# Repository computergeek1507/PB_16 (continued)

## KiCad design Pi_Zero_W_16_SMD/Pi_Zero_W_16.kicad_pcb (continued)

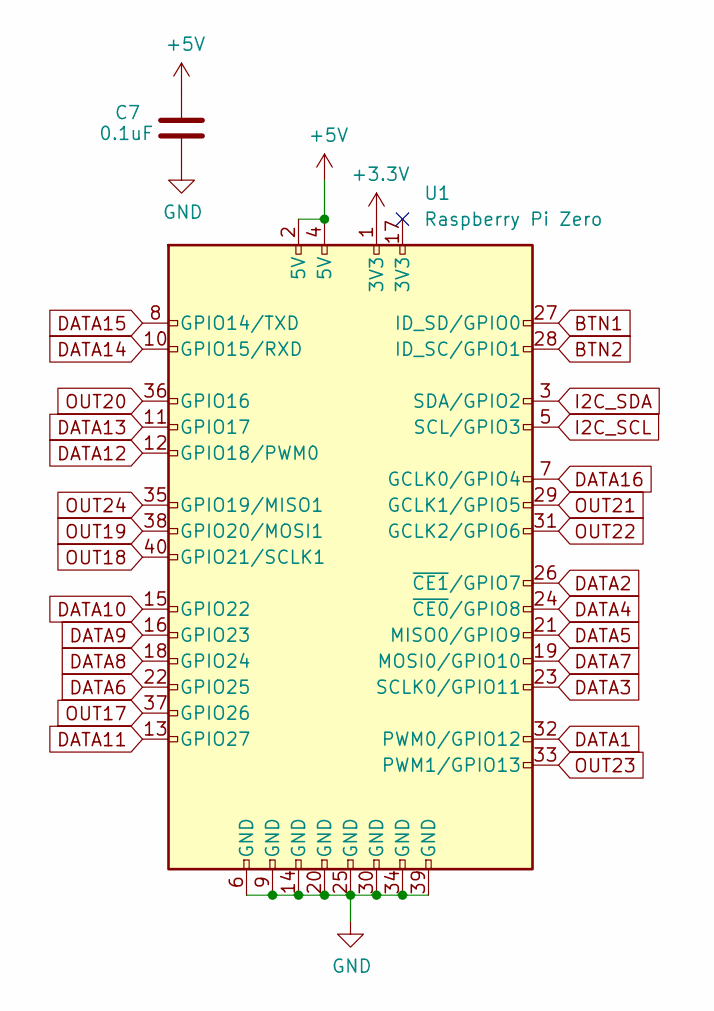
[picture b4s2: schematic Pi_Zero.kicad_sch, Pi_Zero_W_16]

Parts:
C7: 0.1uF; C_0603_1608Metric_Pad1.08x0.95mm_HandSolder
U1: Raspberry Pi Zero; Raspberry_Pi_Zero_Socketed_THT_FaceDown_MountingHoles

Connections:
+3V3: U1.1 (3V3); also elsewhere on the board
+5V: C7.1, U1.2 (5V), U1.4 (5V); also elsewhere on the board
BTN1: U1.27 (ID_SD/GPIO0); also elsewhere on the board
BTN2: U1.28 (ID_SC/GPIO1); also elsewhere on the board
DATA1: U1.32 (PWM0/GPIO12); also elsewhere on the board
DATA2: U1.26 (~CE1/GPIO7); also elsewhere on the board
DATA3: U1.23 (SCLK0/GPIO11); also elsewhere on the board
DATA4: U1.24 (~CE0/GPIO8); also elsewhere on the board
DATA5: U1.21 (MISO0/GPIO9); also elsewhere on the board
DATA6: U1.22 (GPIO25); also elsewhere on the board
DATA7: U1.19 (MOSI0/GPIO10); also elsewhere on the board
DATA8: U1.18 (GPIO24); also elsewhere on the board
DATA9: U1.16 (GPIO23); also elsewhere on the board
DATA10: U1.15 (GPIO22); also elsewhere on the board
DATA11: U1.13 (GPIO27); also elsewhere on the board
DATA12: U1.12 (GPIO18/PWM0); also elsewhere on the board
DATA13: U1.11 (GPIO17); also elsewhere on the board
DATA14: U1.10 (GPIO15/RXD); also elsewhere on the board
DATA15: U1.8 (GPIO14/TXD); also elsewhere on the board
DATA16: U1.7 (GCLK0/GPIO4); also elsewhere on the board
GND: C7.2, U1.6 (GND), U1.9 (GND), U1.14 (GND), U1.20 (GND), U1.25 (GND), U1.30 (GND), U1.34 (GND), U1.39 (GND); also elsewhere on the board
I2C_SCL: U1.5 (SCL/GPIO3); also elsewhere on the board
I2C_SDA: U1.3 (SDA/GPIO2); also elsewhere on the board
OUT17: U1.37 (GPIO26); also elsewhere on the board
OUT18: U1.40 (GPIO21/SCLK1); also elsewhere on the board
OUT19: U1.38 (GPIO20/MOSI1); also elsewhere on the board
OUT20: U1.36 (GPIO16); also elsewhere on the board
OUT21: U1.29 (GCLK1/GPIO5); also elsewhere on the board
OUT22: U1.31 (GCLK2/GPIO6); also elsewhere on the board
OUT23: U1.33 (PWM1/GPIO13); also elsewhere on the board
OUT24: U1.35 (GPIO19/MISO1); also elsewhere on the board

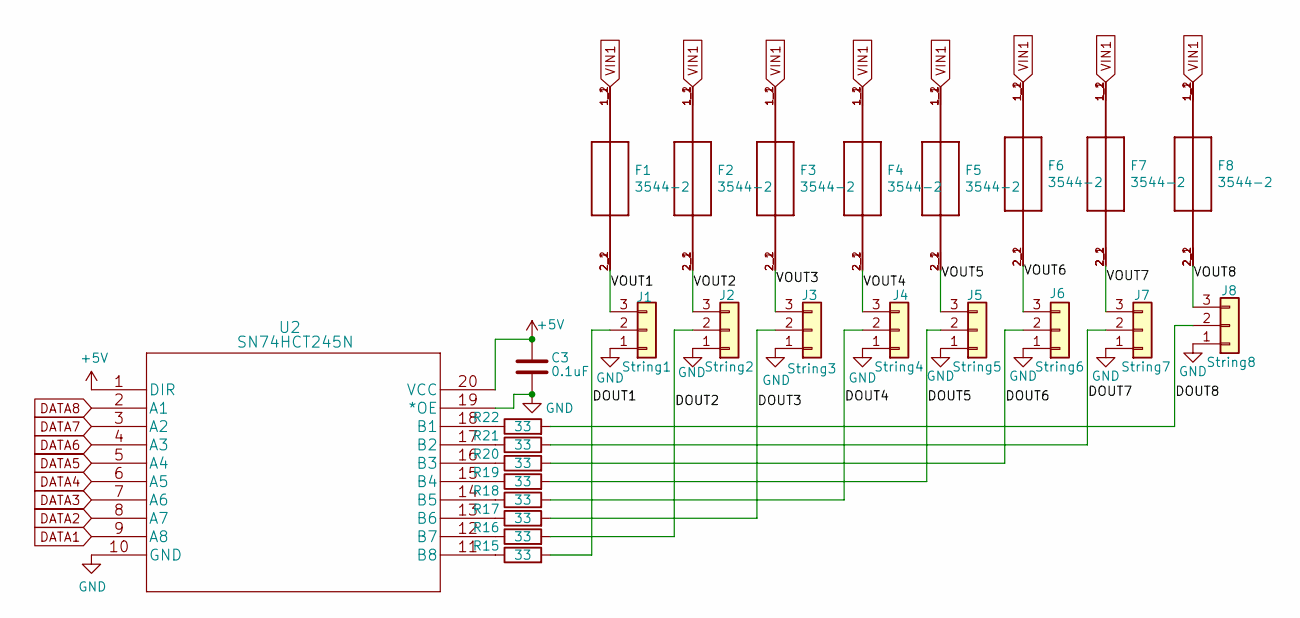
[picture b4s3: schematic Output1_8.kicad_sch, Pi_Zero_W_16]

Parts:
C3: 0.1uF; C_0603_1608Metric_Pad1.08x0.95mm_HandSolder; MPN CL10B104KB8NNWC; Digi-Key_PN 1276-1935-2-ND
F1, F2, F3, F4, F5, F6, F7, F8: 3544-2; FUSE_3544-2; MPN 3544-2; Digi-Key_PN 36-3544-2-ND
J1: String1; PhoenixContact_MCV_3.81mm_3.5mm_1x03_Vertical; MPN 1843619/OSTTJ0311530; Digi-Key_PN 277-5737-ND/ED10555-ND
J2: String2; PhoenixContact_MCV_3.81mm_3.5mm_1x03_Vertical; MPN 1843619/OSTTJ0311530; Digi-Key_PN 277-5737-ND/ED10555-ND
J3: String3; PhoenixContact_MCV_3.81mm_3.5mm_1x03_Vertical; MPN 1843619/OSTTJ0311530; Digi-Key_PN 277-5737-ND/ED10555-ND
J4: String4; PhoenixContact_MCV_3.81mm_3.5mm_1x03_Vertical; MPN 1843619/OSTTJ0311530; Digi-Key_PN 277-5737-ND/ED10555-ND
J5: String5; PhoenixContact_MCV_3.81mm_3.5mm_1x03_Vertical; MPN 1843619/OSTTJ0311530; Digi-Key_PN 277-5737-ND/ED10555-ND
J6: String6; PhoenixContact_MCV_3.81mm_3.5mm_1x03_Vertical; MPN 1843619/OSTTJ0311530; Digi-Key_PN 277-5737-ND/ED10555-ND
J7: String7; PhoenixContact_MCV_3.81mm_3.5mm_1x03_Vertical; MPN 1843619/OSTTJ0311530; Digi-Key_PN 277-5737-ND/ED10555-ND
J8: String8; PhoenixContact_MCV_3.81mm_3.5mm_1x03_Vertical; MPN 1843619/OSTTJ0311530; Digi-Key_PN 277-5737-ND/ED10555-ND
R15, R16, R17, R18, R19, R20, R21, R22: 33; R_0603_1608Metric_Pad0.98x0.95mm_HandSolder; MPN RC0603FR-0733RL; LCSC C23140
U2: SN74HCT245N; SN74HCT245NSR; MPN SN74HCT245NSR; Digi-Key_PN 296-15849-1-ND

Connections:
+5V: C3.1, U2.1 (DIR), U2.20 (VCC); also elsewhere on the board
/Output 1-8/DOUT1: J1.2, R15.2
/Output 1-8/DOUT2: J2.2, R16.2
/Output 1-8/DOUT3: J3.2, R17.2
/Output 1-8/DOUT4: J4.2, R18.2
/Output 1-8/DOUT5: J5.2, R19.2
/Output 1-8/DOUT6: J6.2, R20.2
/Output 1-8/DOUT7: J7.2, R21.2
/Output 1-8/DOUT8: J8.2, R22.2
/Output 1-8/VOUT1: F1.2_1 (2), F1.2_2 (2), J1.3
/Output 1-8/VOUT2: F2.2_1 (2), F2.2_2 (2), J2.3
/Output 1-8/VOUT3: F3.2_1 (2), F3.2_2 (2), J3.3
/Output 1-8/VOUT4: F4.2_1 (2), F4.2_2 (2), J4.3
/Output 1-8/VOUT5: F5.2_1 (2), F5.2_2 (2), J5.3
/Output 1-8/VOUT6: F6.2_1 (2), F6.2_2 (2), J6.3
/Output 1-8/VOUT7: F7.2_1 (2), F7.2_2 (2), J7.3
/Output 1-8/VOUT8: F8.2_1 (2), F8.2_2 (2), J8.3
DATA1: U2.9 (A8); also elsewhere on the board
DATA2: U2.8 (A7); also elsewhere on the board
DATA3: U2.7 (A6); also elsewhere on the board
DATA4: U2.6 (A5); also elsewhere on the board
DATA5: U2.5 (A4); also elsewhere on the board
DATA6: U2.4 (A3); also elsewhere on the board
DATA7: U2.3 (A2); also elsewhere on the board
DATA8: U2.2 (A1); also elsewhere on the board
GND: C3.2, J1.1, J2.1, J3.1, J4.1, J5.1, J6.1, J7.1, J8.1, U2.10 (GND), U2.19 (*OE); also elsewhere on the board
unnamed: R15.1, U2.11 (B8)
unnamed: R16.1, U2.12 (B7)
unnamed: R17.1, U2.13 (B6)
unnamed: R18.1, U2.14 (B5)
unnamed: R19.1, U2.15 (B4)
unnamed: R20.1, U2.16 (B3)
unnamed: R21.1, U2.17 (B2)
unnamed: R22.1, U2.18 (B1)
VIN1: F1.1_1 (1), F1.1_2 (1), F2.1_1 (1), F2.1_2 (1), F3.1_1 (1), F3.1_2 (1), F4.1_1 (1), F4.1_2 (1), F5.1_1 (1), F5.1_2 (1), F6.1_1 (1), F6.1_2 (1), F7.1_1 (1), F7.1_2 (1), F8.1_1 (1), F8.1_2 (1); also elsewhere on the board

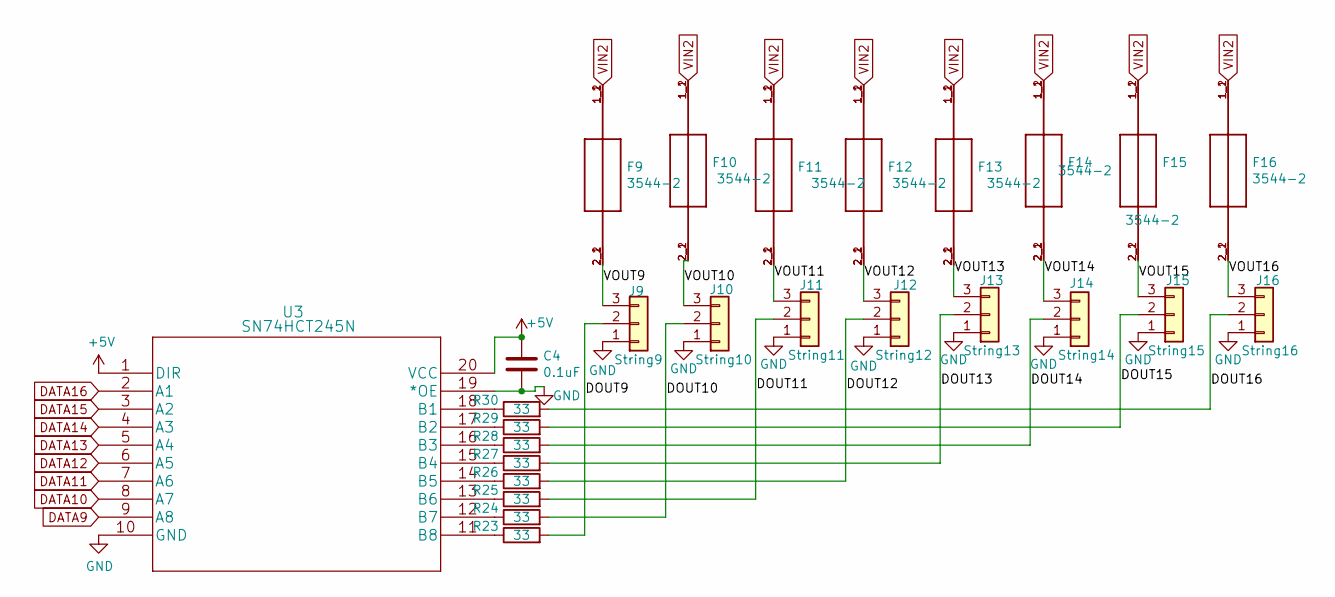
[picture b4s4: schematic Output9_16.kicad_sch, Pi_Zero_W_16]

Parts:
C4: 0.1uF; C_0603_1608Metric_Pad1.08x0.95mm_HandSolder; MPN CL10B104KB8NNWC; Digi-Key_PN 1276-1935-2-ND
F9, F10, F11, F12, F13, F14, F15, F16: 3544-2; FUSE_3544-2; MPN 3544-2; Digi-Key_PN 36-3544-2-ND
J9: String9; PhoenixContact_MCV_3.81mm_3.5mm_1x03_Vertical; MPN 1843619/OSTTJ0311530; Digi-Key_PN 277-5737-ND/ED10555-ND
J10: String10; PhoenixContact_MCV_3.81mm_3.5mm_1x03_Vertical; MPN 1843619/OSTTJ0311530; Digi-Key_PN 277-5737-ND/ED10555-ND
J11: String11; PhoenixContact_MCV_3.81mm_3.5mm_1x03_Vertical; MPN 1843619/OSTTJ0311530; Digi-Key_PN 277-5737-ND/ED10555-ND
J12: String12; PhoenixContact_MCV_3.81mm_3.5mm_1x03_Vertical; MPN 1843619/OSTTJ0311530; Digi-Key_PN 277-5737-ND/ED10555-ND
J13: String13; PhoenixContact_MCV_3.81mm_3.5mm_1x03_Vertical; MPN 1843619/OSTTJ0311530; Digi-Key_PN 277-5737-ND/ED10555-ND
J14: String14; PhoenixContact_MCV_3.81mm_3.5mm_1x03_Vertical; MPN 1843619/OSTTJ0311530; Digi-Key_PN 277-5737-ND/ED10555-ND
J15: String15; PhoenixContact_MCV_3.81mm_3.5mm_1x03_Vertical; MPN 1843619/OSTTJ0311530; Digi-Key_PN 277-5737-ND/ED10555-ND
J16: String16; PhoenixContact_MCV_3.81mm_3.5mm_1x03_Vertical; MPN 1843619/OSTTJ0311530; Digi-Key_PN 277-5737-ND/ED10555-ND
R23, R24, R25, R26, R27, R28, R29, R30: 33; R_0603_1608Metric_Pad0.98x0.95mm_HandSolder; MPN RC0603FR-0733RL; LCSC C23140
U3: SN74HCT245N; SN74HCT245NSR; MPN SN74HCT245NSR; Digi-Key_PN 296-15849-1-ND

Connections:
+5V: C4.1, U3.1 (DIR), U3.20 (VCC); also elsewhere on the board
/Output 9-16/DOUT9: J9.2, R23.2
/Output 9-16/DOUT10: J10.2, R24.2
/Output 9-16/DOUT11: J11.2, R25.2
/Output 9-16/DOUT12: J12.2, R26.2
/Output 9-16/DOUT13: J13.2, R27.2
/Output 9-16/DOUT14: J14.2, R28.2
/Output 9-16/DOUT15: J15.2, R29.2
/Output 9-16/DOUT16: J16.2, R30.2
/Output 9-16/VOUT9: F9.2_1 (2), F9.2_2 (2), J9.3
/Output 9-16/VOUT10: F10.2_1 (2), F10.2_2 (2), J10.3
/Output 9-16/VOUT11: F11.2_1 (2), F11.2_2 (2), J11.3
/Output 9-16/VOUT12: F12.2_1 (2), F12.2_2 (2), J12.3
/Output 9-16/VOUT13: F13.2_1 (2), F13.2_2 (2), J13.3
/Output 9-16/VOUT14: F14.2_1 (2), F14.2_2 (2), J14.3
/Output 9-16/VOUT15: F15.2_1 (2), F15.2_2 (2), J15.3
/Output 9-16/VOUT16: F16.2_1 (2), F16.2_2 (2), J16.3
DATA9: U3.9 (A8); also elsewhere on the board
DATA10: U3.8 (A7); also elsewhere on the board
DATA11: U3.7 (A6); also elsewhere on the board
DATA12: U3.6 (A5); also elsewhere on the board
DATA13: U3.5 (A4); also elsewhere on the board
DATA14: U3.4 (A3); also elsewhere on the board
DATA15: U3.3 (A2); also elsewhere on the board
DATA16: U3.2 (A1); also elsewhere on the board
GND: C4.2, J9.1, J10.1, J11.1, J12.1, J13.1, J14.1, J15.1, J16.1, U3.10 (GND), U3.19 (*OE); also elsewhere on the board
unnamed: R23.1, U3.11 (B8)
unnamed: R24.1, U3.12 (B7)
unnamed: R25.1, U3.13 (B6)
unnamed: R26.1, U3.14 (B5)
unnamed: R27.1, U3.15 (B4)
unnamed: R28.1, U3.16 (B3)
unnamed: R29.1, U3.17 (B2)
unnamed: R30.1, U3.18 (B1)
VIN2: F9.1_1 (1), F9.1_2 (1), F10.1_1 (1), F10.1_2 (1), F11.1_1 (1), F11.1_2 (1), F12.1_1 (1), F12.1_2 (1), F13.1_1 (1), F13.1_2 (1), F14.1_1 (1), F14.1_2 (1), F15.1_1 (1), F15.1_2 (1), F16.1_1 (1), F16.1_2 (1); also elsewhere on the board

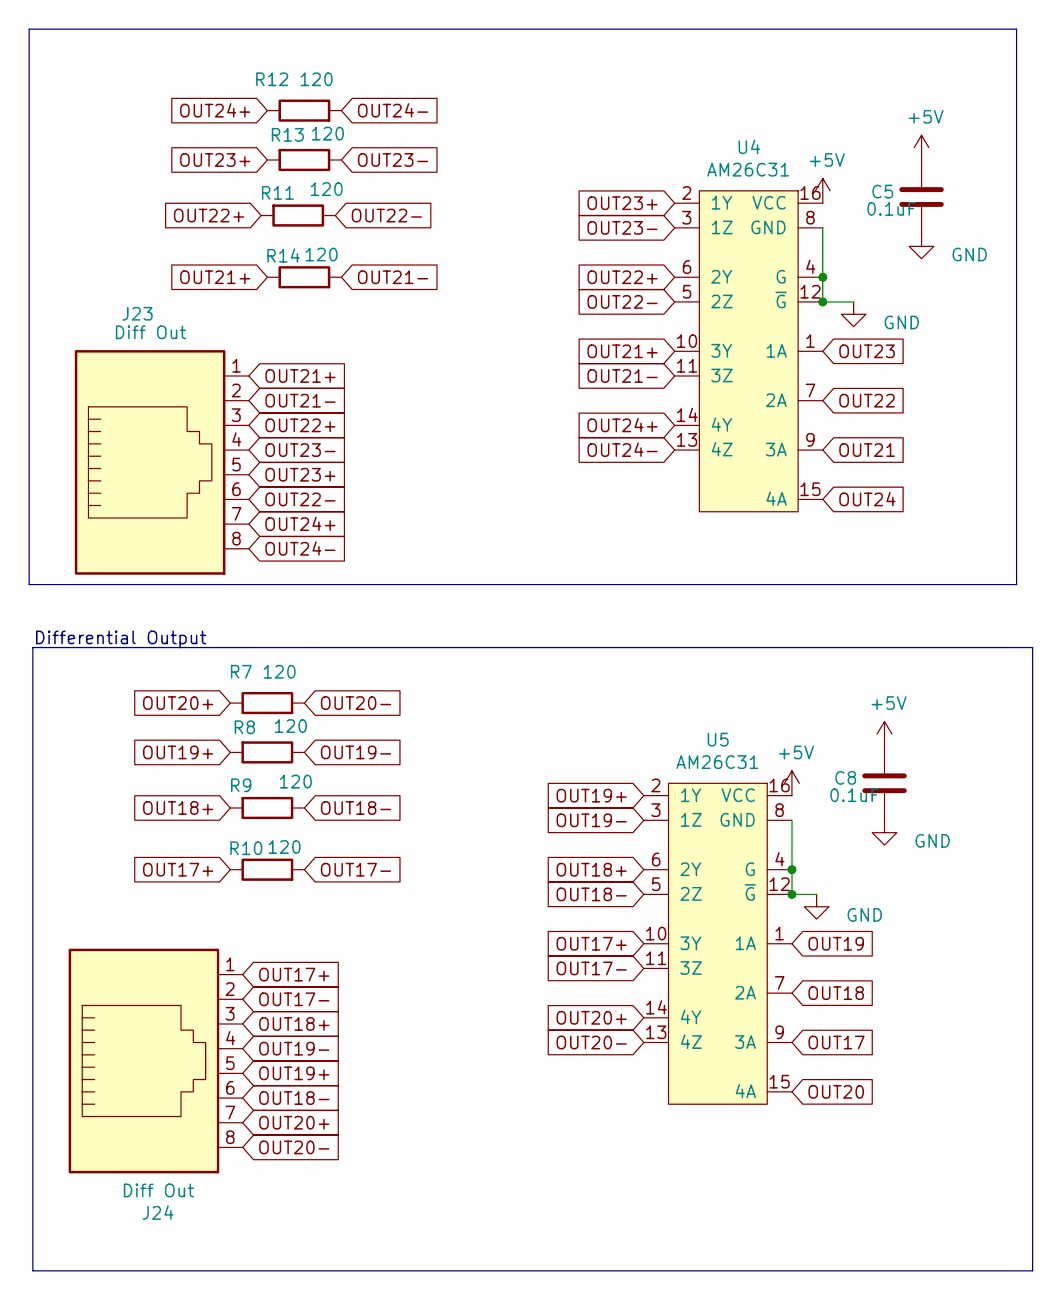
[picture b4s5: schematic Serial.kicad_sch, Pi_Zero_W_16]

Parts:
C5, C8: 0.1uF; C_0603_1608Metric_Pad1.08x0.95mm_HandSolder; MPN CL10B104KB8NNWC; Digi-Key_PN 1276-1935-2-ND
J23, J24: Diff Out; RJ45_Amphenol_54602-x08_Horizontal; MPN X05ADIWA1DY1022; Digi-Key_PN AE10392-ND
R7, R8, R9, R10, R11, R12, R13, R14: 120; R_0603_1608Metric_Pad0.98x0.95mm_HandSolder; MPN CRGCQ0603F120R; Digi-Key_PN A129677CT-ND
U4, U5: AM26C31; SOIC-16_3.9x9.9mm_P1.27mm; MPN AM26C31IDR; Farnell 4975637

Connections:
+5V: C5.1, C8.1, U4.16 (VCC), U5.16 (VCC); also elsewhere on the board
GND: C5.2, C8.2, U4.4 (G), U4.8 (GND), U4.12 (~G), U5.4 (G), U5.8 (GND), U5.12 (~G); also elsewhere on the board
OUT17: U5.9 (3A); also elsewhere on the board
OUT17+: J24.1, R10.1, U5.10 (3Y)
OUT17-: J24.2, R10.2, U5.11 (3Z)
OUT18: U5.7 (2A); also elsewhere on the board
OUT18+: J24.3, R9.2, U5.6 (2Y)
OUT18-: J24.6, R9.1, U5.5 (2Z)
OUT19: U5.1 (1A); also elsewhere on the board
OUT19+: J24.5, R8.2, U5.2 (1Y)
OUT19-: J24.4, R8.1, U5.3 (1Z)
OUT20: U5.15 (4A); also elsewhere on the board
OUT20+: J24.7, R7.1, U5.14 (4Y)
OUT20-: J24.8, R7.2, U5.13 (4Z)
OUT21: U4.9 (3A); also elsewhere on the board
OUT21+: J23.1, R14.1, U4.10 (3Y)
OUT21-: J23.2, R14.2, U4.11 (3Z)
OUT22: U4.7 (2A); also elsewhere on the board
OUT22+: J23.3, R11.2, U4.6 (2Y)
OUT22-: J23.6, R11.1, U4.5 (2Z)
OUT23: U4.1 (1A); also elsewhere on the board
OUT23+: J23.5, R13.2, U4.2 (1Y)
OUT23-: J23.4, R13.1, U4.3 (1Z)
OUT24: U4.15 (4A); also elsewhere on the board
OUT24+: J23.7, R12.1, U4.14 (4Y)
OUT24-: J23.8, R12.2, U4.13 (4Z)

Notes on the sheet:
Differential Output

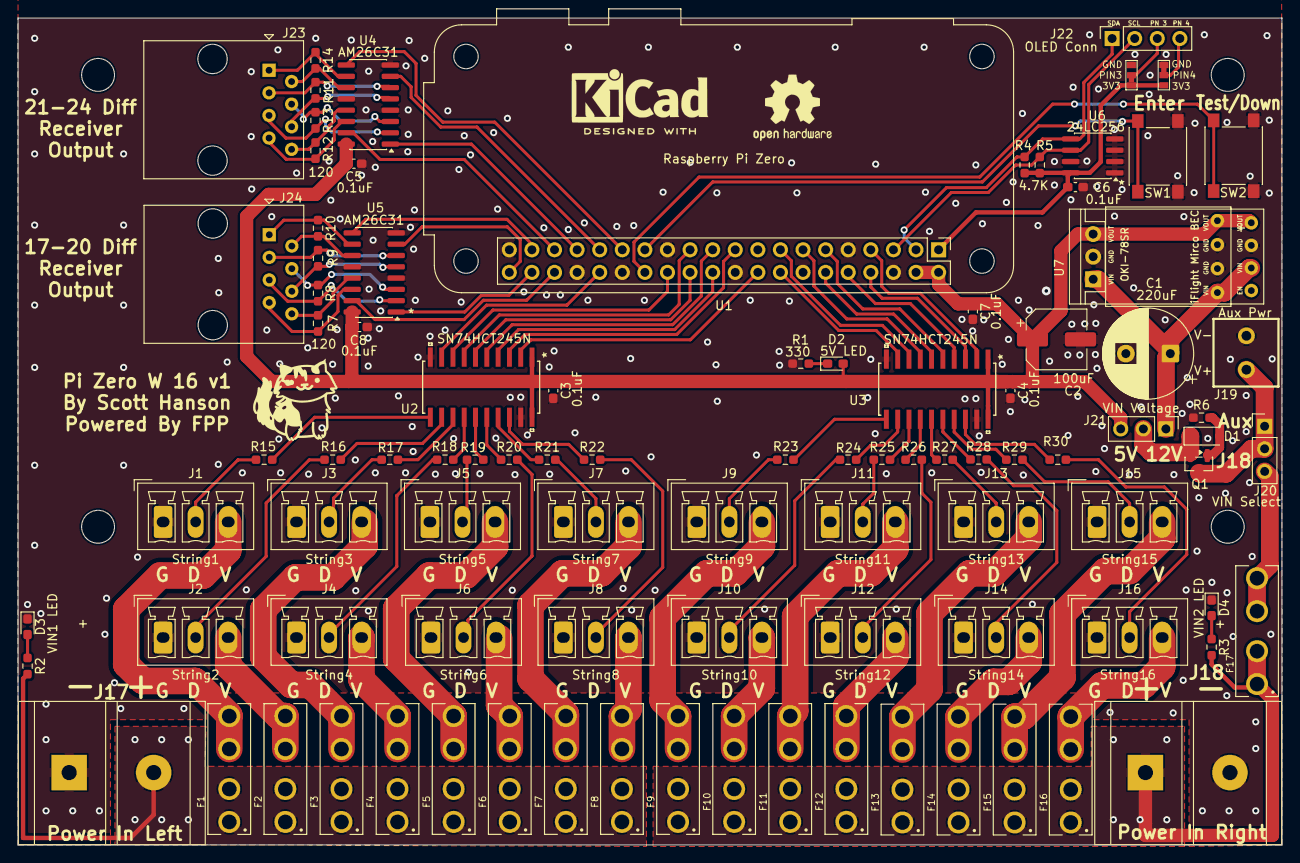
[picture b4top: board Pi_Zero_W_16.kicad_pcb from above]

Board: 2 copper layers, 142.1 x 93.0 mm, 99 parts (1 on the bottom side), 107 nets.

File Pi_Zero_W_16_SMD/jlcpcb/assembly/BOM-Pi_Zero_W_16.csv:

Comment,Designator,Footprint,LCSC
Enter BTN,"SW1,SW2",SW_Push_1P1T_NO_6x6mm_H9.5mm,C127509
SN74HCT245N,"U2,U3",SN74HCT245NSR,C133641
100uF,C2,CP_Elec_6.3x5.4_Nichicon,C134723
0.1uF,"C3,C4,C5,C6,C7,C8",C_0603_1608Metric_Pad1.08x0.95mm_HandSolder,C14663
DMP3056L,Q1,SOT-23,C150724
AM26C31,"U4,U5",SOIC-16_3.9x9.9mm_P1.27mm,C157476
Zener 10V,D1,D_SOD-123,C173431
OLED Conn,J22,PinSocket_1x04_P2.54mm_Vertical,C225501
120,"R10,R11,R12,R13,R14,R7,R8,R9",R_0603_1608Metric_Pad0.98x0.95mm_HandSolder,C22787
5V LED,"D2,D3,D4",LED_0603_1608Metric_Pad1.05x0.95mm_HandSolder,C2286
330,R1,R_0603_1608Metric_Pad0.98x0.95mm_HandSolder,C23138
33,"R15,R16,R17,R18,R19,R20,R21,R22,R23,R24,R25,R26,R27,R28,R29,R30",R_0603_1608Metric_Pad0.98x0.95mm_HandSolder,C23140
4.7K,"R4,R5",R_0603_1608Metric_Pad0.98x0.95mm_HandSolder,C23162
100K,R6,R_0603_1608Metric_Pad0.98x0.95mm_HandSolder,C25803
Diff Out,"J23,J24",RJ45_Amphenol_54602-x08_Horizontal,C2938579
220uF,C1,CP_Radial_D10.0mm_P5.00mm,C338228
2K,"R2,R3",R_0603_1608Metric_Pad0.98x0.95mm_HandSolder,C4190
VIN Select,"J20,J21",PinHeader_1x03_P2.54mm_Vertical,C49257
3544-2,"F1,F10,F11,F12,F13,F14,F15,F16,F17,F2,F3,F4,F5,F6,F7,F8,F9",FUSE_3544-2,C492610
24LC256,U6,SOIC-8_3.9x4.9mm_P1.27mm,C6482
Aux Pwr,J19,PHOENIX_MKDS1_2-3.81,C69811
Power In Left,"J17,J18",BARRIER_BLOCK_1ROW_2POS_P9.5MM,C707421
String1,"J1,J10,J11,J12,J13,J14,J15,J16,J2,J3,J4,J5,J6,J7,J8,J9",PhoenixContact_MCV_3.81mm_3.5mm_1x03_Vertical,C8389
Universe5V,U7,Universal_5V_Horizontal,
Raspberry Pi Zero,U1,Raspberry_Pi_Zero_Socketed_THT_FaceDown_MountingHoles,

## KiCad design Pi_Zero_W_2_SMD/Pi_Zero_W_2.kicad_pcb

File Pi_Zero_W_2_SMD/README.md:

# Copyright and Disclaimer
Copyright: Scott Hanson

This documentation describes Open Hardware and is licensed under the CERN Open Hardware Licence Version 2 - Strongly Reciprocal. (CERN-OHL-S)

You may redistribute and modify this documentation under the terms of the CERN OHL-S-v2 (https://ohwr.org/cern_ohl_s_v2.txt). This documentation is distributed WITHOUT ANY EXPRESS OR IMPLIED WARRANTY, INCLUDING OF MERCHANTABILITY, SATISFACTORY QUALITY AND FITNESS FOR A PARTICULAR PURPOSE. Please see the CERN OHL v2-S for applicable conditions

**Under CERN OHL-S-v2, derivative work must be publicy released as defined in subsection 3.3**

# Pi Zero W 2

**Never Built or tested**

The Pi Zero W 2 is a surface mount(SMD) controller with 2 local pixel ports. All the design files are open source and available on github.

## [Interactive BOM](https://computergeek1507.github.io/PB_16/Pi_Zero_W_2_SMD/bom/ibom)

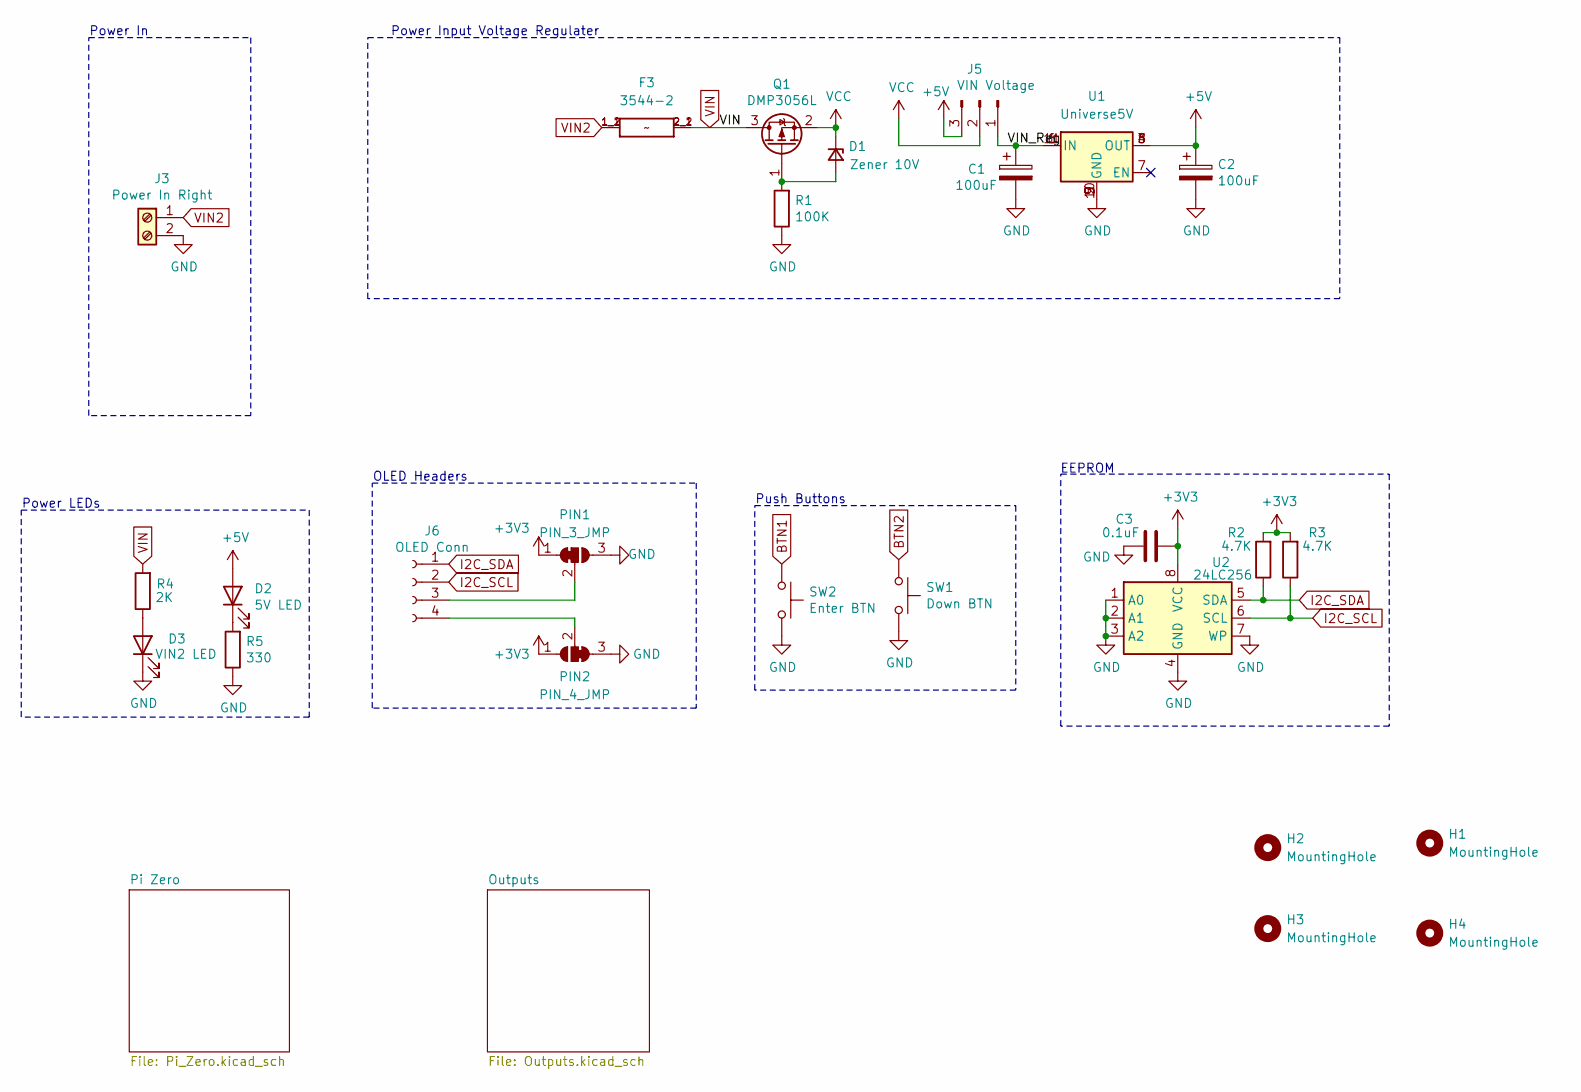
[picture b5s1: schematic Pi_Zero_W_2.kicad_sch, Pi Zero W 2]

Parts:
C1, C2: 100uF; CP_Elec_6.3x5.4_Nichicon; MPN UWX1C101MCL1GB; Digi-Key_PN 493-2105-1-ND
C3: 0.1uF; C_0603_1608Metric; MPN CL10B104KB8NNWC; Digi-Key_PN 1276-1935-2-ND
D1: Zener 10V; D_SOD-123; MPN MMSZ5240B-7-F; Digi-Key_PN MMSZ5240B-FDICT-ND
D2: 5V LED; LED_0603_1608Metric; MPN LTST-C190KRKT; Digi-Key_PN 160-1436-2-ND
D3: VIN2 LED; LED_0603_1608Metric; MPN LTST-C190KRKT; Digi-Key_PN 160-1436-2-ND
F3: 3544-2; FUSE_3544-2; MPN 3544-2; Digi-Key_PN 36-3544-2-ND
H1, H2, H3, H4: MountingHole; MountingHole_3.7mm
J3: Power In Right; BARRIER_BLOCK_1ROW_2POS_P8.26MM; LCSC C306200
J5: VIN Voltage; PinHeader_1x03_P2.54mm_Vertical; MPN 61300311121; Digi-Key_PN 732-5316-ND
J6: OLED Conn; PinSocket_1x04_P2.54mm_Vertical; MPN PPTC041LFBN-RC; Digi-Key_PN S7002-ND
PIN1: PIN_3_JMP; SolderJumper-3_P1mm_Bridged12
PIN2: PIN_4_JMP; SolderJumper-3_P1mm_Bridged23
Q1: DMP3056L; SOT-23; MPN DMP3056L-7; Digi-Key_PN DMP3056L-7DICT-ND
R1: 100K; R_0603_1608Metric; MPN RT0603BRD07100KL; Digi-Key_PN YAG1235CT-ND
R2, R3: 4.7K; R_0603_1608Metric; MPN RC0603JR-074K7L; Digi-Key_PN 311-4.7KGRCT-ND
R4: 2K; R_0603_1608Metric; LCSC C4190
R5: 330; R_0603_1608Metric; LCSC C23138
SW1: Down BTN; SW_Push_1P1T_NO_6x6mm_H9.5mm; MPN PTS645SL50SMTR92 LFS; Digi-Key_PN CKN9088CT-ND
SW2: Enter BTN; SW_Push_1P1T_NO_6x6mm_H9.5mm; MPN PTS645SL50SMTR92 LFS; Digi-Key_PN CKN9088CT-ND
U1: Universe5V; Universal_5V_Horizontal
U2: 24LC256; SOIC-8_3.9x4.9mm_P1.27mm; MPN 24LC256T-I/SN; Digi-Key_PN 24LC256T-I/SNCT-ND

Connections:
+3V3: C3.1, PIN1.1 (A), PIN2.1 (A), R2.2, R3.2, U2.8 (VCC); also elsewhere on the board
+5V: C2.1, D2.2 (A), J5.3, U1.3 (OUT), U1.4 (OUT), U1.8 (OUT); also elsewhere on the board
/VIN_Reg: C1.1, J5.1, U1.1 (IN), U1.6 (IN), U1.11 (IN)
BTN1: SW2.1; also elsewhere on the board
BTN2: SW1.1; also elsewhere on the board
GND: C1.2, C2.2, C3.2, D3.1 (K), J3.2, PIN1.3 (B), PIN2.3 (B), R1.1, R5.1, SW1.2, SW2.2, U1.2 (GND), U1.5 (GND), U1.9 (GND), U1.10 (GND), U2.1 (A0), U2.2 (A1), U2.3 (A2), U2.4 (GND), U2.7 (WP); also elsewhere on the board
I2C_SCL: J6.2, R3.1, U2.6 (SCL); also elsewhere on the board
I2C_SDA: J6.1, R2.1, U2.5 (SDA); also elsewhere on the board
unnamed: D1.2 (A), Q1.1 (G), R1.2
unnamed: D2.1 (K), R5.2
unnamed: D3.2 (A), R4.1
unnamed: J6.3, PIN1.2 (C)
unnamed: J6.4, PIN2.2 (C)
VCC: D1.1 (K), J5.2, Q1.2 (S)
VIN: F3.2_1 (2), F3.2_2 (2), Q1.3 (D), R4.2
VIN2: F3.1_1 (1), F3.1_2 (1), J3.1; also elsewhere on the board

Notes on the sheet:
Power LEDs
Power In
OLED Headers
Push Buttons
Power Input Voltage Regulater
EEPROM

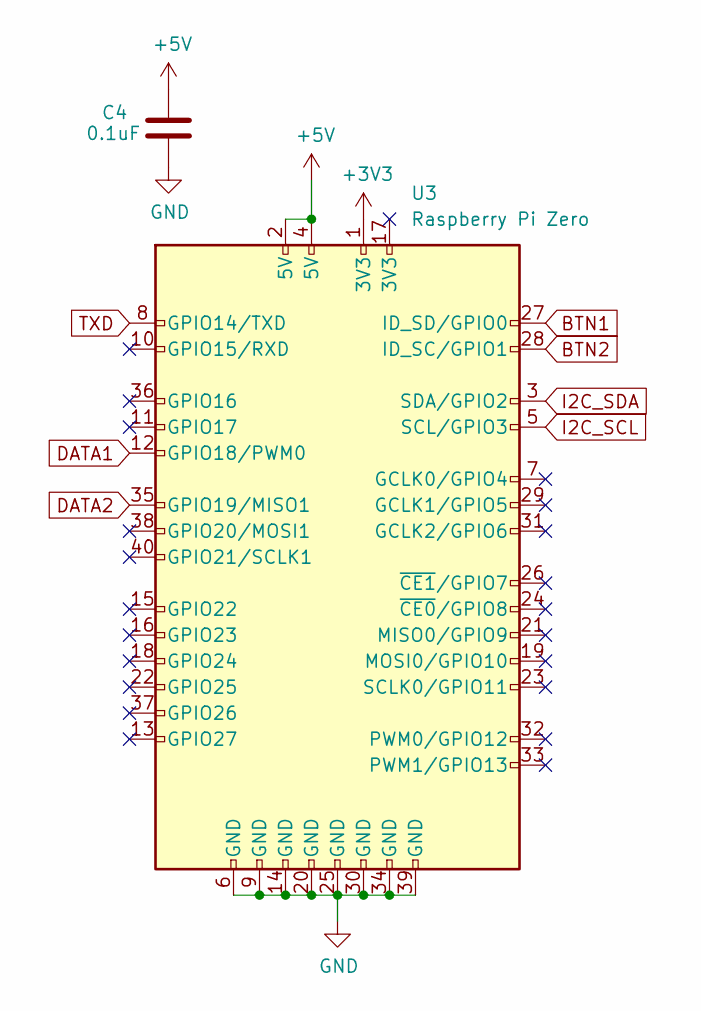
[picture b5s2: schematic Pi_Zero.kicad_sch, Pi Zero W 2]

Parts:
C4: 0.1uF; C_0603_1608Metric; MPN CL10B104KB8NNWC; Digi-Key_PN 1276-1935-2-ND
U3: Raspberry Pi Zero; Raspberry_Pi_Zero_Socketed_THT_FaceDown_MountingHoles

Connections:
+3V3: U3.1 (3V3); also elsewhere on the board
+5V: C4.1, U3.2 (5V), U3.4 (5V); also elsewhere on the board
BTN1: U3.27 (ID_SD/GPIO0); also elsewhere on the board
BTN2: U3.28 (ID_SC/GPIO1); also elsewhere on the board
DATA1: U3.12 (GPIO18/PWM0); also elsewhere on the board
DATA2: U3.35 (GPIO19/MISO1); also elsewhere on the board
GND: C4.2, U3.6 (GND), U3.9 (GND), U3.14 (GND), U3.20 (GND), U3.25 (GND), U3.30 (GND), U3.34 (GND), U3.39 (GND); also elsewhere on the board
I2C_SCL: U3.5 (SCL/GPIO3); also elsewhere on the board
I2C_SDA: U3.3 (SDA/GPIO2); also elsewhere on the board
TXD: U3.8 (GPIO14/TXD); also elsewhere on the board

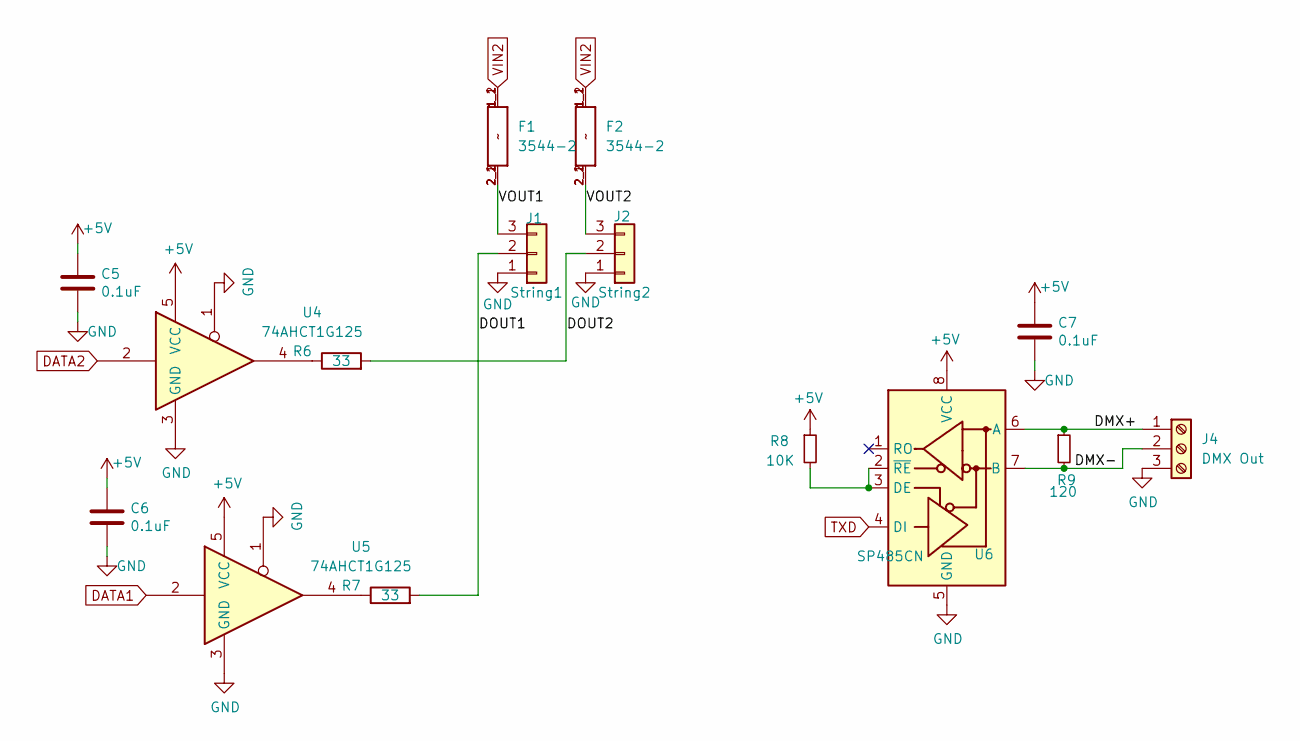
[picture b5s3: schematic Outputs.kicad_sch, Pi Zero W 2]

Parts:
C5, C6, C7: 0.1uF; C_0603_1608Metric; MPN CL10B104KB8NNWC; Digi-Key_PN 1276-1935-2-ND
F1, F2: 3544-2; FUSE_3544-2; MPN 3544-2; Digi-Key_PN 36-3544-2-ND
J1: String1; PhoenixContact_MCV_3.81mm_3.5mm_1x03_Vertical; MPN 1843619/OSTTJ0311530; Digi-Key_PN 277-5737-ND/ED10555-ND
J2: String2; PhoenixContact_MCV_3.81mm_3.5mm_1x03_Vertical; MPN 1843619/OSTTJ0311530; Digi-Key_PN 277-5737-ND/ED10555-ND
J4: DMX Out; TerminalBlock_Phoenix_MKDS-1,5-3-5.08_1x03_P5.08mm_Horizont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
R6, R7: 33; R_0603_1608Metric; MPN RC0603FR-0733RL; LCSC C23140
R8: 10K; R_0603_1608Metric; LCSC C25804
R9: 120; R_0603_1608Metric; LCSC C22790
U4, U5: 74AHCT1G125; TSOP-5_1.65x3.05mm_P0.95mm; LCSC C7484
U6: SP485CN; SOIC-8_3.9x4.9mm_P1.27mm; MPN SP485CN-L/TR; Digi-Key_PN 1016-1825-1-ND

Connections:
+5V: C5.1, C6.1, C7.1, R8.1, U4.5 (VCC), U5.5 (VCC), U6.8 (VCC); also elsewhere on the board
/Outputs/DMX+: J4.1, R9.1, U6.6 (A)
/Outputs/DMX-: J4.2, R9.2, U6.7 (B)
/Outputs/DOUT1: J1.2, R7.2
/Outputs/DOUT2: J2.2, R6.2
/Outputs/VOUT1: F1.2_1 (2), F1.2_2 (2), J1.3
/Outputs/VOUT2: F2.2_1 (2), F2.2_2 (2), J2.3
DATA1: U5.2; also elsewhere on the board
DATA2: U4.2; also elsewhere on the board
GND: C5.2, C6.2, C7.2, J1.1, J2.1, J4.3, U4.1, U4.3 (GND), U5.1, U5.3 (GND), U6.5 (GND); also elsewhere on the board
unnamed: R6.1, U4.4
unnamed: R7.1, U5.4
unnamed: R8.2, U6.2 (~RE), U6.3 (DE)
TXD: U6.4 (DI); also elsewhere on the board
VIN2: F1.1_1 (1), F1.1_2 (1), F2.1_1 (1), F2.1_2 (1); also elsewhere on the board

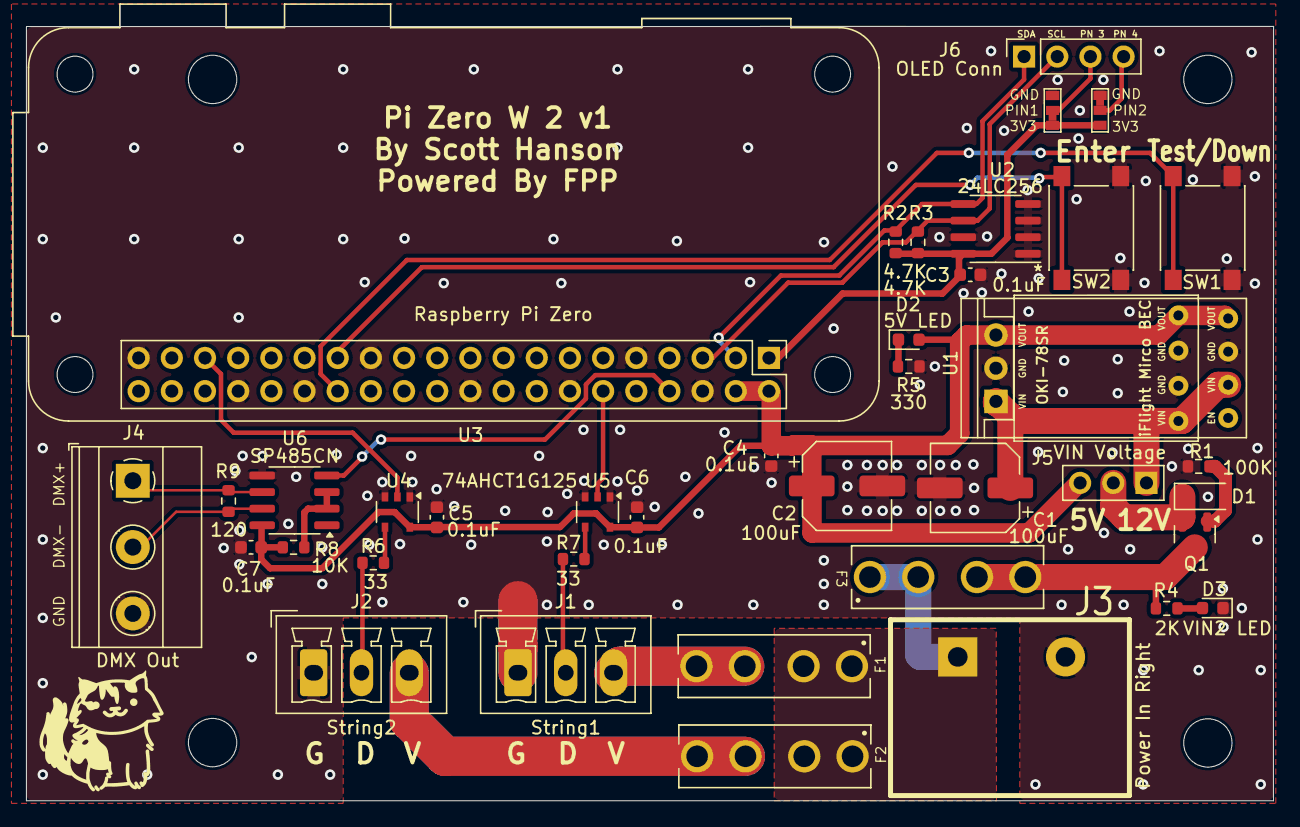
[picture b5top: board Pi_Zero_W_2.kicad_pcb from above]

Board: 2 copper layers, 95.5 x 59.3 mm, 43 parts (1 on the bottom side), 28 nets.

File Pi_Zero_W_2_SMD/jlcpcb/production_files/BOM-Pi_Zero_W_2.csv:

Comment,Designator,Footprint,LCSC,Quantity
Down BTN,"SW1,SW2",SW_Push_1P1T_NO_6x6mm_H9.5mm,C127509,2
100uF,"C1,C2",CP_Elec_6.3x5.4_Nichicon,C134723,2
0.1uF,"C3,C4,C5,C6,C7",C_0603_1608Metric,C14663,5
DMP3056L,Q1,SOT-23,C150724,1
Zener 10V,D1,D_SOD-123,C173431,1
OLED Conn,J6,PinSocket_1x04_P2.54mm_Vertical,C225501,1
120,R9,R_0603_1608Metric,C22790,1
5V LED,"D2,D3",LED_0603_1608Metric,C2286,2
330,R5,R_0603_1608Metric,C23138,1
33,"R6,R7",R_0603_1608Metric,C23140,2
4.7K,"R2,R3",R_0603_1608Metric,C23162,2
100K,R1,R_0603_1608Metric,C25803,1
10K,R8,R_0603_1608Metric,C25804,1
DMX Out,J4,"TerminalBlock_Phoenix_MKDS-1,5-3-5.08_1x03_P5.08mm_Horizontal",C3018699,1
Power In Right,J3,BARRIER_BLOCK_1ROW_2POS_P8.26MM,C306200,1
2K,R4,R_0603_1608Metric,C4190,1
VIN Voltage,J5,PinHeader_1x03_P2.54mm_Vertical,C49257,1
3544-2,"F1,F2,F3",FUSE_3544-2,C492610,3
24LC256,U2,SOIC-8_3.9x4.9mm_P1.27mm,C6482,1
SP485CN,U6,SOIC-8_3.9x4.9mm_P1.27mm,C6855,1
74AHCT1G125,"U4,U5",TSOP-5_1.65x3.05mm_P0.95mm,C7484,2
String1,"J1,J2",PhoenixContact_MCV_3.81mm_3.5mm_1x03_Vertical,C8389,2
Universe5V,U1,Universal_5V_Horizontal,,1
PIN_3_JMP,PIN1,SolderJumper-3_P1mm_Bridged12,,1
PIN_4_JMP,PIN2,SolderJumper-3_P1mm_Bridged23,,1
Raspberry Pi Zero,U3,Raspberry_Pi_Zero_Socketed_THT_FaceDown_MountingHoles,,1

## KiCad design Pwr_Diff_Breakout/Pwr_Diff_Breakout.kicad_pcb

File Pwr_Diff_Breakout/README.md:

# Copyright and Disclaimer
Copyright: Scott Hanson

This documentation describes Open Hardware and is licensed under the CERN Open Hardware License Version 2 - Strongly Reciprocal. (CERN-OHL-S)

You may redistribute and modify this documentation under the terms of the CERN OHL-S-v2 (https://ohwr.org/cern_ohl_s_v2.txt). This documentation is distributed WITHOUT ANY EXPRESS OR IMPLIED WARRANTY, INCLUDING OF MERCHANTABILITY, SATISFACTORY QUALITY AND FITNESS FOR A PARTICULAR PURPOSE. Please see the CERN OHL v2-S for applicable conditions

**Under CERN OHL-S-v2, derivative work must be publicly released as defined in subsection 3.3**

# Pwr Diff Breakout

The "Pwr Diff Breakout" board has four single Differental Reciever outputs with power on two CAT5 pins. It pugs in to a 4 output differental output. It works with the "Single_Receiver_Out". All the design files are open source and available on github.

## [Part BOM](https://github.com/computergeek1507/PB_16/raw/master/Pwr_Diff_Breakout/Pwr_Diff_Breakout_BOM.ods)

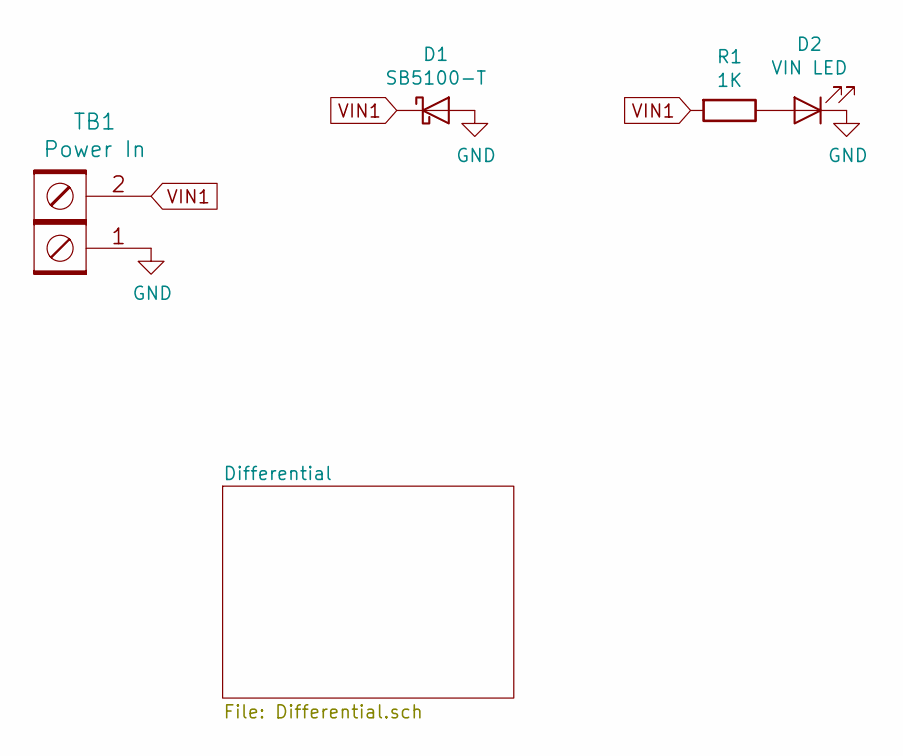
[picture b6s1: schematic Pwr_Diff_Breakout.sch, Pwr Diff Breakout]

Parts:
D1: SB5100-T; D_DO-201AD_P12.70mm_Horizontal; MPN SB5100-T; Digi-Key_PN SB5100DICT-ND
D2: VIN LED; LED_D3.0mm_Clear; MPN WP3A8GD; Digi-Key_PN 754-1217-ND
R1: 1K; R_Axial_DIN0207_L6.3mm_D2.5mm_P7.62mm_Horizontal; MPN CF14JT1K00; Digi-Key_PN CF14JT1K00CT-ND
TB1: Power In; BARRIER_BLOCK_1ROW_2POS_P8.26MM; MPN 4DB-P108-02; Digi-Key_PN A98472-ND

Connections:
GND: D1.2 (A), D2.1 (K), TB1.1; also elsewhere on the board
unnamed: D2.2 (A), R1.1
VIN1: D1.1 (K), R1.2, TB1.2; also elsewhere on the board
